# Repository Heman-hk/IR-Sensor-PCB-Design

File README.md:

#  IR Sensor Module – LM358 Based

This project implements a simple **Infrared (IR) proximity sensor** using an IR LED, photodiode, and an LM358 operational amplifier configured as a voltage comparator. Designed for object detection tasks, the circuit generates a digital output when IR light is reflected from a nearby surface.

---

##  Circuit Description

- **IR LED** emits infrared light continuously.
- **Photodiode** receives reflected IR light and generates a corresponding voltage signal.
- **LM358 Op-Amp** compares the photodiode signal with an adjustable reference voltage (set by RV1).
- **Output Pin (0/P)** goes HIGH when an object is detected (voltage crosses the threshold).

---

##  Components

| Component   | Description                            |
|------------|----------------------------------------|
| IR LED      | Infrared emitter for sensing          |
| Photodiode  | Reflective light detector              |
| LM358       | Dual Op-Amp IC used in comparator mode|
| Resistors   | R1, R2, R3 to set gain and bias        |
| Potentiometer (RV1) | Sensitivity threshold adjust |
| Output Pin  | Digital signal when object is detected|

---
##  Applications

- Obstacle detection for robotics
- Line-following robot modules
- Hand gesture triggers
- Proximity detection for automation

---

##  Notes

- Adjust RV1 for optimal sensitivity under ambient lighting
- Ensure IR LED and photodiode are mounted parallel to detect reflected light
- Output can be interfaced directly with microcontrollers (e.g., ESP32, Arduino)

---

##  Designed By

**Himanshu Kumar**  
Embedded Systems & Circuit Design Enthusiast

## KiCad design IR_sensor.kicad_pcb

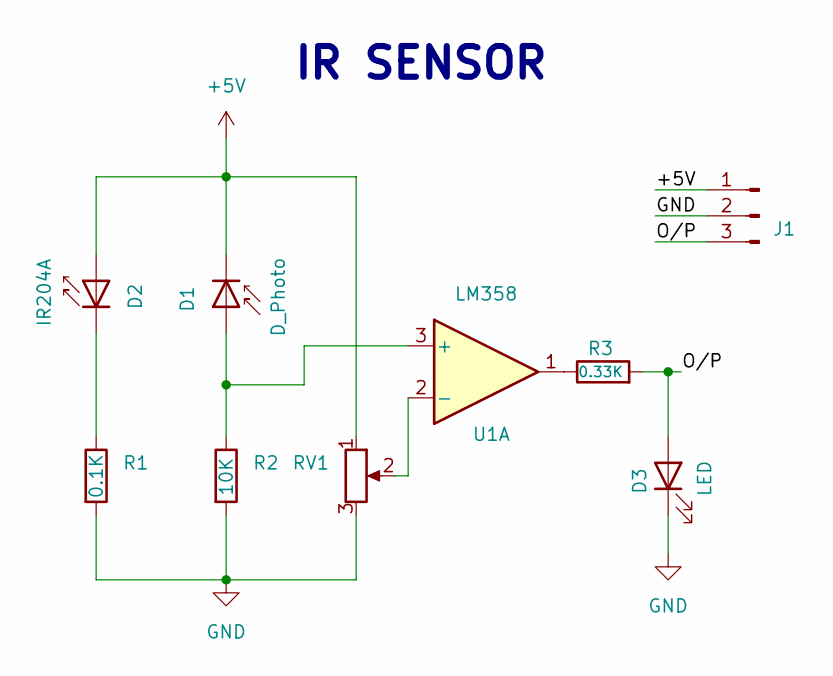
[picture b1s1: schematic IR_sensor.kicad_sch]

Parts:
D1: D_Photo; D_SOD-123
D2: IR204A; LED_1206_3216Metric
D3: LED; LED_0603_1608Metric
J1: Conn_01x03_Pin; Stocko_MKS_1653-6-0-303_1x3_P2.50mm_Vertical
R1: 0.1K; R_0603_1608Metric
R2: 10K; R_0603_1608Metric
R3: 0.33K; R_0603_1608Metric
RV1: 10K; Potentiometer_Bourns_TC33X_Vertical
U1: LM358; SOIC-4_4.55x2.6mm_P1.27mm

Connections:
+5V: D1.1 (K), D2.2 (A), J1.1, RV1.1
/O/P: D3.2 (A), J1.3, R3.2
GND: D3.1 (K), J1.2, R1.2, R2.2, RV1.3
unnamed: D1.2 (A), R2.1, U1.3 (+)
unnamed: D2.1 (K), R1.1
unnamed: R3.1, U1.1
unnamed: RV1.2, U1.2 (-)

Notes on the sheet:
IR SENSOR

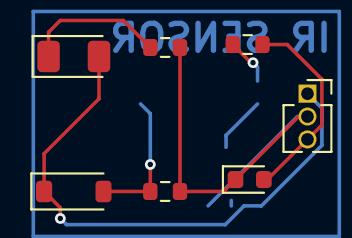
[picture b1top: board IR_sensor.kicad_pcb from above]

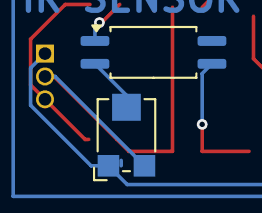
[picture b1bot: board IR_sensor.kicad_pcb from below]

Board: 2 copper layers, 9 parts (2 on the bottom side), 7 nets.
